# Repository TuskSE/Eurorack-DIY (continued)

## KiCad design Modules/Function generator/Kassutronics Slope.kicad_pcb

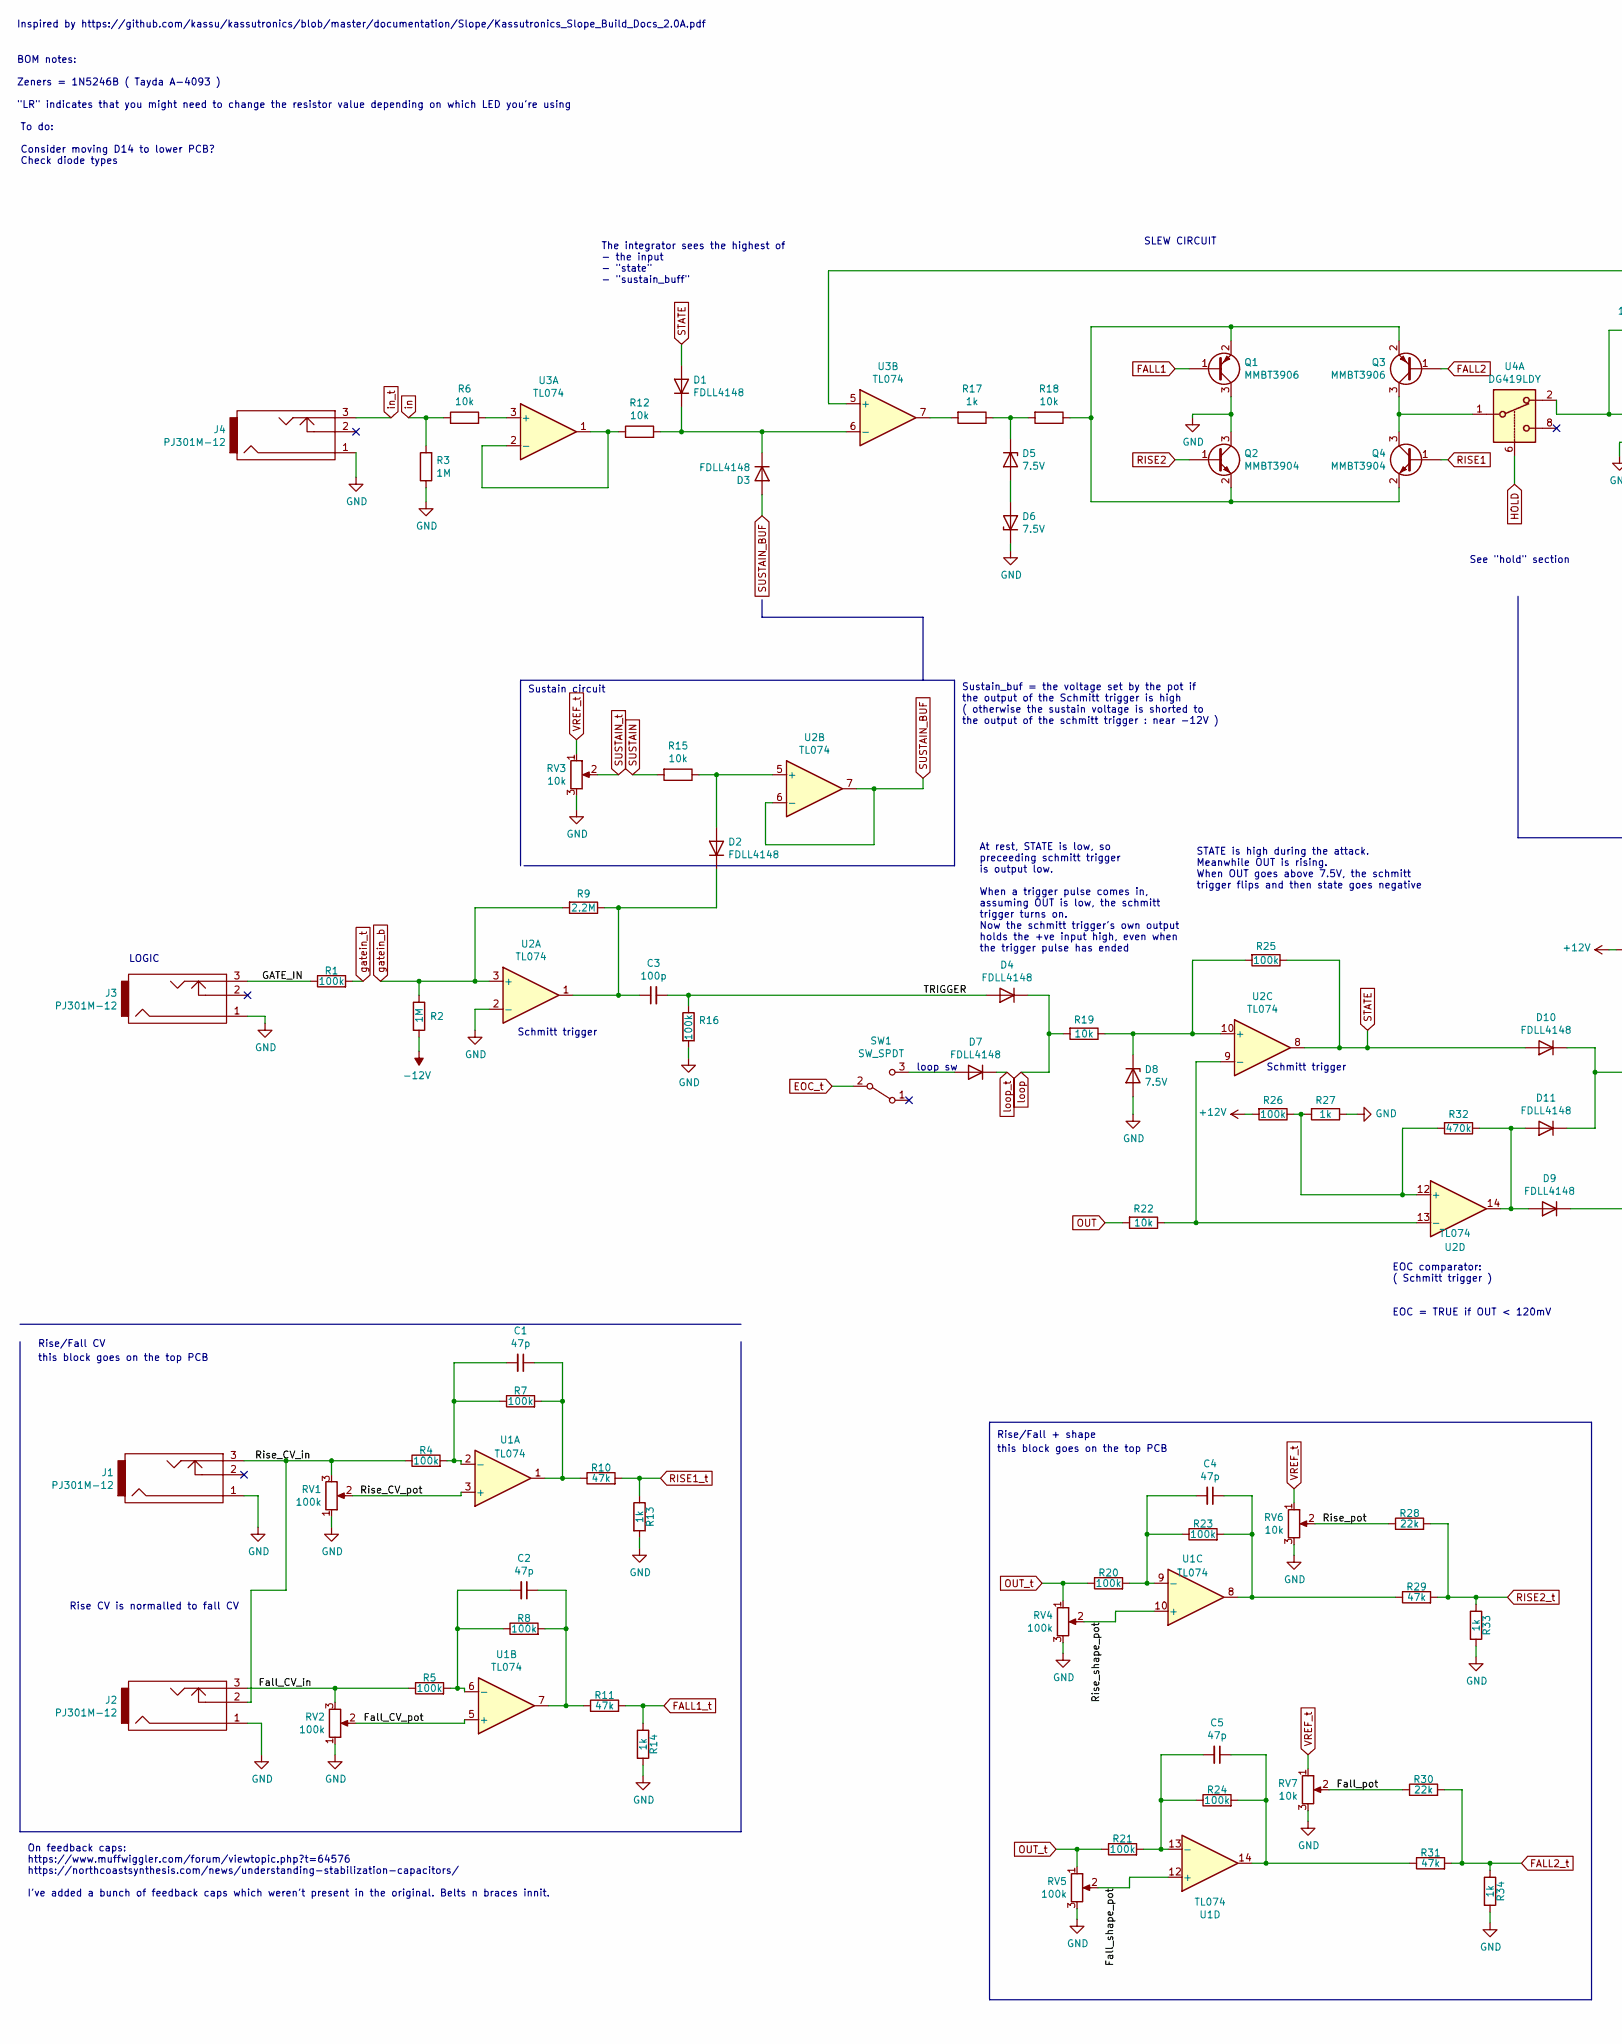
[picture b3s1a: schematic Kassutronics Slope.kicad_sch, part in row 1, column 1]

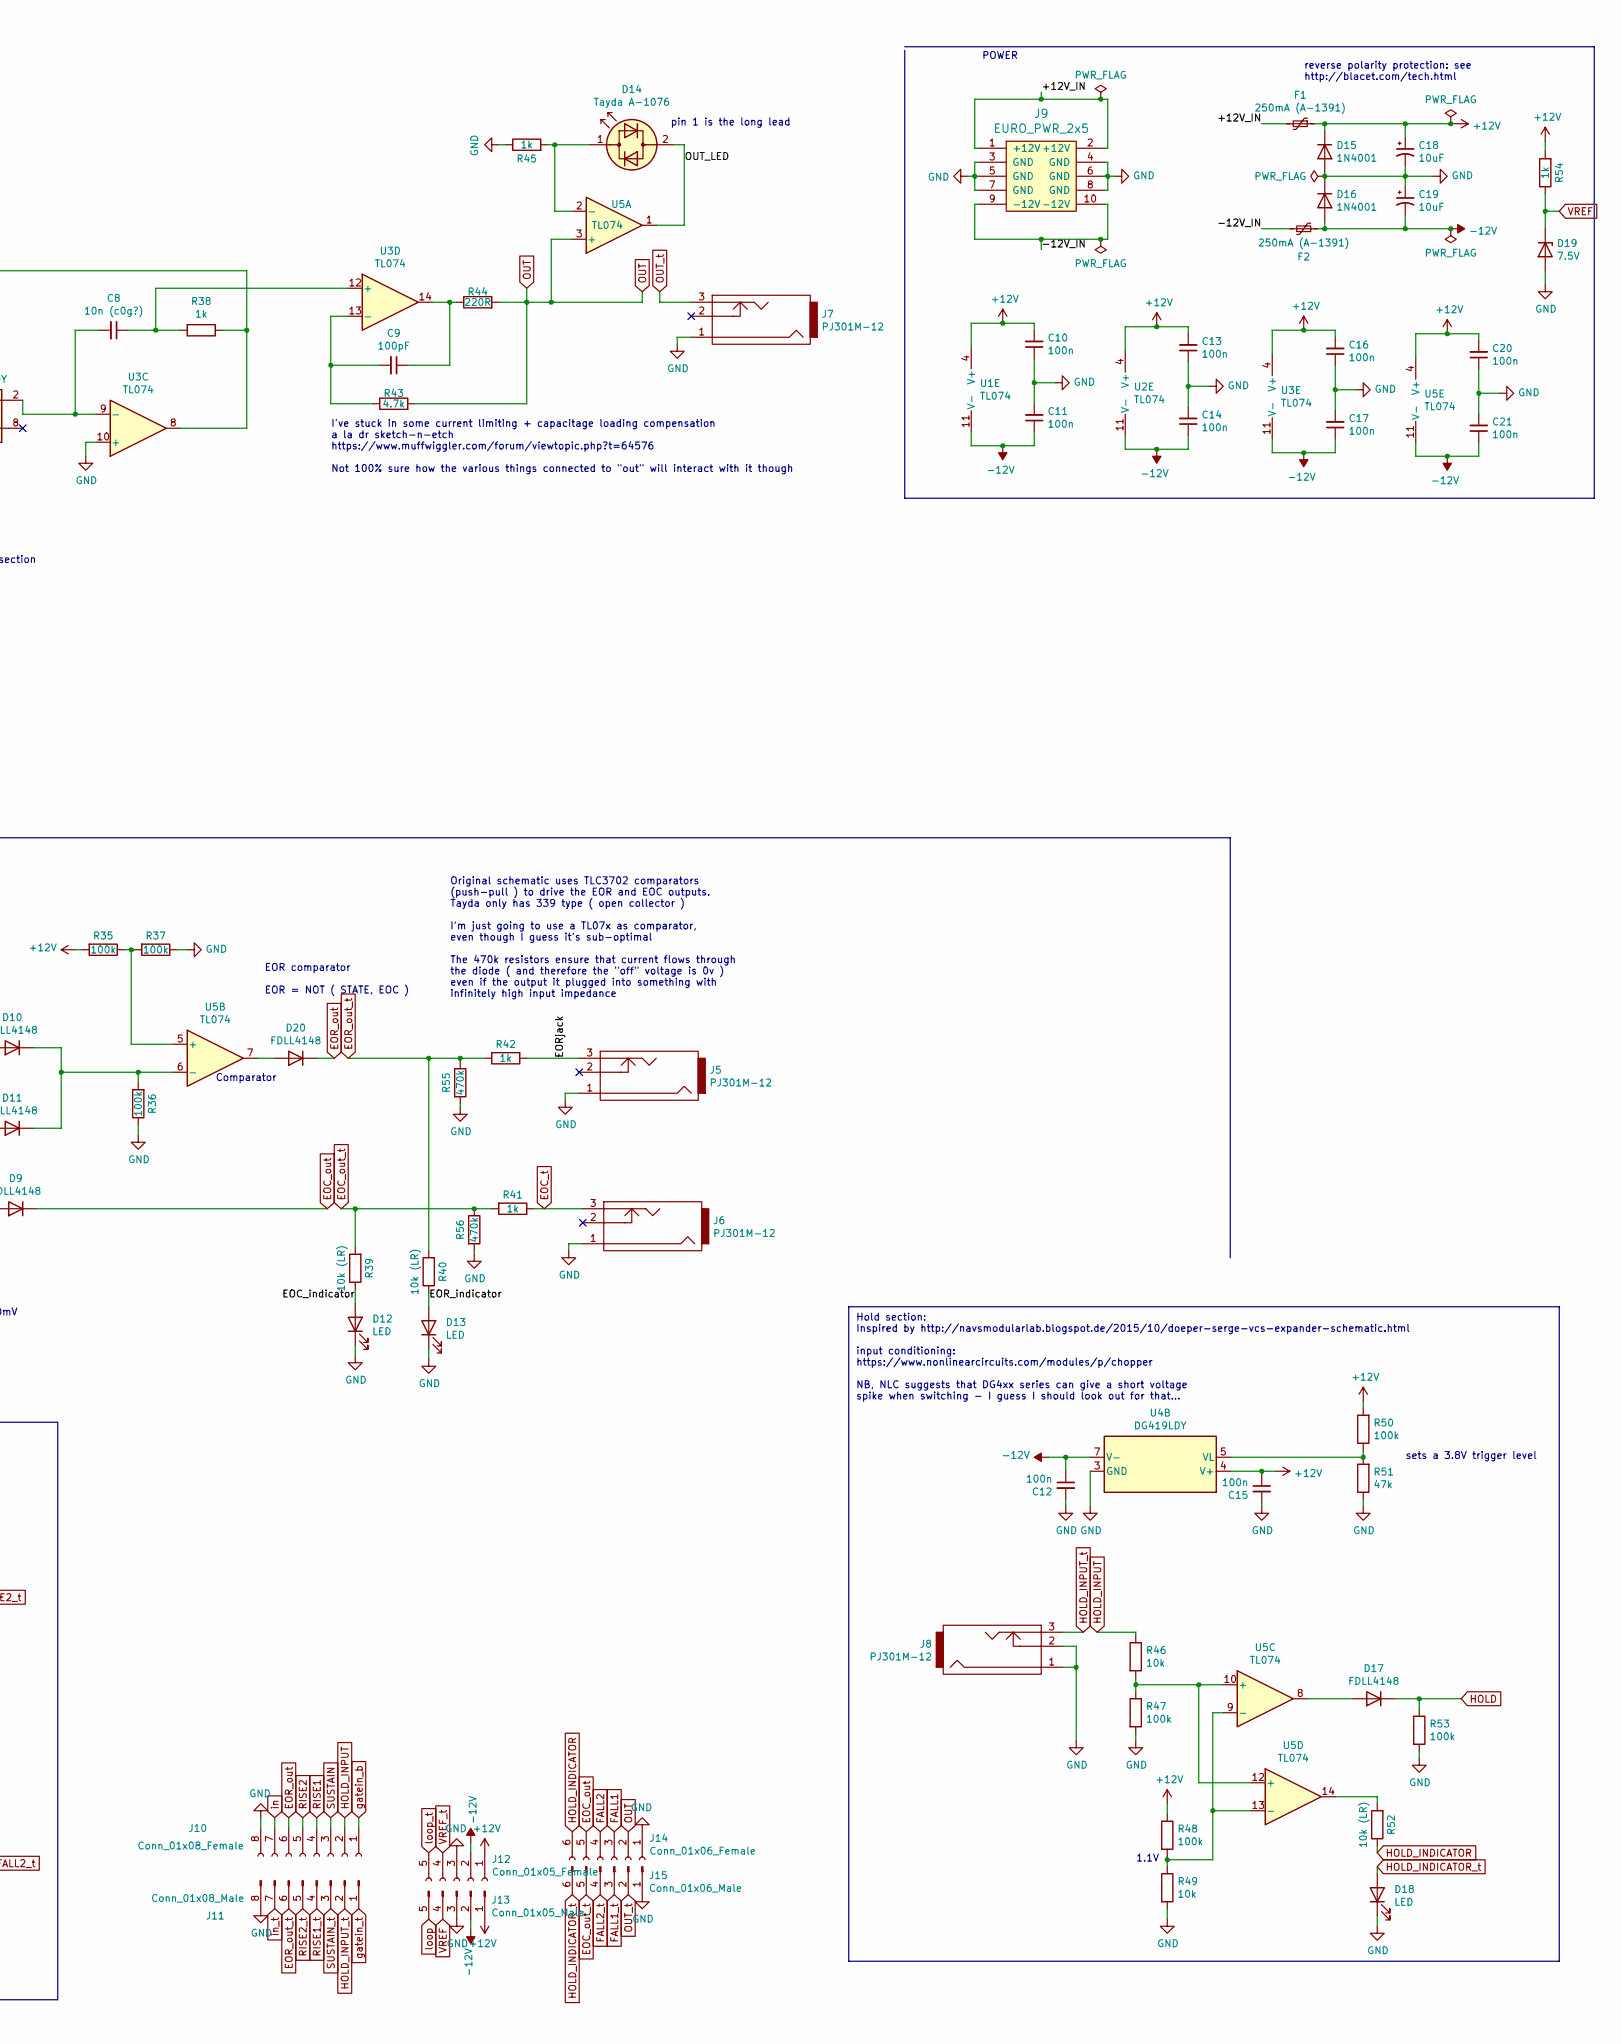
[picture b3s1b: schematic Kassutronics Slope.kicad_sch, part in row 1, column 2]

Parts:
C1, C2, C4, C5: 47p; C_0805_2012Metric_Pad1.15x1.40mm_HandSolder_smallText
C3: 100p; C_0805_2012Metric_Pad1.15x1.40mm_HandSolder_smallText
C8: 10n (c0g?); C_0805_2012Metric_Pad1.15x1.40mm_HandSolder_smallText
C9: 100pF; C_0805_2012Metric_Pad1.15x1.40mm_HandSolder_smallText
C10, C11, C12, C13, C14, C15, C16, C17, C20, C21: 100n; C_0805_2012Metric_Pad1.15x1.40mm_HandSolder_smallText
C18, C19: 10uF; CP_Radial_D5.0mm_P2.00mm
D1, D2, D3, D4, D7, D9, D10, D11, D17, D20: FDLL4148; LL4148_sam
D5, D6, D8, D19: 7.5V; D_DO-35_SOD27_P7.62mm_Horizontal
D12, D13, D18: LED; LED_D3.0mm
D14: Tayda A-1076; LED_D3.0mm
D15, D16: 1N4001; D_DO-41_SOD81_P10.16mm_Horizontal
F1, F2: 250mA (A-1391); C_Disc_D7.5mm_W2.5mm_P5.00mm
J1, J2, J3, J4, J5, J6, J7, J8: PJ301M-12; PJ301M-12_Compact
J9: EURO_PWR_2x5; Eurorack_power_header
J10: Conn_01x08_Female; PinHeader_1x08_P2.54mm_Vertical
J11: Conn_01x08_Male; PinHeader_1x08_P2.54mm_Vertical
J12: Conn_01x05_Female; PinHeader_1x05_P2.54mm_Vertical
J13: Conn_01x05_Male; PinHeader_1x05_P2.54mm_Vertical
J14: Conn_01x06_Female; PinHeader_1x06_P2.54mm_Vertical
J15: Conn_01x06_Male; PinHeader_1x06_P2.54mm_Vertical
Q1, Q3: MMBT3906; SOT-23
Q2, Q4: MMBT3904; SOT-23
R1, R4, R5, R7, R8, R16, R20, R21, R23, R24, R25, R26, R35, R36, R37, R47, R48, R50, R53: 100k; R_0805_2012Metric_Pad1.15x1.40mm_HandSolder_smallText
R2, R3: 1M; R_0805_2012Metric_Pad1.15x1.40mm_HandSolder_smallText
R6, R12, R15, R18, R19, R22, R46, R49: 10k; R_0805_2012Metric_Pad1.15x1.40mm_HandSolder_smallText
R9: 2.2M; R_0805_2012Metric_Pad1.15x1.40mm_HandSolder_smallText
R10, R11, R29, R31, R51: 47k; R_0805_2012Metric_Pad1.15x1.40mm_HandSolder_smallText
R13, R14, R17, R27, R33, R34, R38, R41, R42, R45, R54: 1k; R_0805_2012Metric_Pad1.15x1.40mm_HandSolder_smallText
R28, R30: 22k; R_0805_2012Metric_Pad1.15x1.40mm_HandSolder_smallText
R32, R55, R56: 470k; R_0805_2012Metric_Pad1.15x1.40mm_HandSolder_smallText
R39, R40, R52: 10k (LR); R_0805_2012Metric_Pad1.15x1.40mm_HandSolder_smallText
R43: 4.7k; R_0805_2012Metric_Pad1.15x1.40mm_HandSolder_smallText
R44: 220R; R_0805_2012Metric_Pad1.15x1.40mm_HandSolder_smallText
RV1, RV2: 100k; Alpha9mmPot
RV3, RV6, RV7: 10k; Alpha9mmPot
RV4, RV5: 100k; SongHuei9mmPot
SW1: SW_SPDT; SPDT toggle on-off-on
U1, U2, U3, U5: TL074; SOIC-14_3.9x8.7mm_P1.27mm
U4: DG419LDY; SOIC-8_3.9x4.9mm_P1.27mm

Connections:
+12V: C10.2, C13.2, C15.1, C16.2, C18.1, C20.2, D15.1 (K), F1.1, J12.1, J13.1, R26.2, R35.2, R48.1, R50.2, R54.2, U1.4 (V+), U2.4 (V+), U3.4 (V+), U4.4 (V+), U5.4 (V+)
-12V: C11.1, C12.1, C14.1, C17.1, C19.2, C21.1, D16.2 (A), F2.2, J12.2, J13.2, R2.2, U1.11 (V-), U2.11 (V-), U3.11 (V-), U4.7 (V-), U5.11 (V-)
/+12V_IN: F1.2, J9.1 (+12V), J9.2 (+12V)
/-12V_IN: F2.1, J9.9 (-12V), J9.10 (-12V)
/EOC_indicator: D12.2 (A), R39.1
/EOR_indicator: D13.2 (A), R40.1
/EORjack: J5.3, R42.1
/Fall_CV_in: J2.3, R5.1, RV2.3
/Fall_CV_pot: RV2.2, U1.5 (+)
/Fall_pot: R30.1, RV7.2
/Fall_shape_pot: RV5.2, U1.12 (+)
/GATE_IN: J3.3, R1.1
/OUT_LED: D14.2 (AK), U5.1
/Rise_CV_in: J1.3, J2.2, R4.1, RV1.3
/Rise_CV_pot: RV1.2, U1.3 (+)
/Rise_pot: R28.1, RV6.2
/Rise_shape_pot: RV4.2, U1.10 (+)
/TRIGGER: C3.2, D4.2 (A), R16.1
EOC_out: D9.1 (K), J14.5
EOC_out_t: J15.5, R39.2, R41.2, R56.1
EOC_t: J6.3, R41.1, SW1.2 (B)
EOR_out: D20.1 (K), J10.6
EOR_out_t: J11.6, R40.2, R42.2, R55.1
FALL1: J14.3, Q1.1 (B)
FALL1_t: J15.3, R11.2, R14.1
FALL2: J14.4, Q3.1 (B)
FALL2_t: J15.4, R30.2, R31.2, R34.1
GND: C10.1, C11.2, C12.2, C13.1, C14.2, C15.2, C16.1, C17.2, C18.2, C19.1, C20.1, C21.2, D6.1 (K), D8.2 (A), D12.1 (K), D13.1 (K), D15.2 (A), D16.1 (K), D18.1 (K), D19.2 (A), J1.1, J2.1, J3.1, J4.1, J5.1, J6.1, J7.1, J8.1, J8.2, J9.3 (GND), J9.4 (GND), J9.5 (GND), J9.6 (GND), J9.7 (GND), J9.8 (GND), J10.8, J11.8, J12.3, J13.3, J14.1, J15.1, Q1.3 (C), Q2.3 (C), R3.1, R13.2, R14.2, R16.2, R27.1, R33.2, R34.2, R36.1, R37.1, R45.1, R47.2, R49.2, R51.1, R53.2, R55.2, R56.2, RV1.1, RV2.1, RV3.3, RV4.3, RV5.3, RV6.3, RV7.3, U2.2 (-), U3.10 (+), U4.3 (GND)
HOLD: D17.1 (K), R53.1, U4.6
HOLD_INDICATOR: J14.6, R52.1
HOLD_INDICATOR_t: D18.2 (A), J15.6
HOLD_INPUT: J10.2, R46.1
HOLD_INPUT_t: J8.3, J11.2
unnamed: C1.1, R7.2, R10.1, U1.1
unnamed: C1.2, R4.2, R7.1, U1.2 (-)
unnamed: C2.1, R8.2, R11.1, U1.7
unnamed: C2.2, R5.2, R8.1, U1.6 (-)
unnamed: C3.1, D2.1 (K), R9.1, U2.1
unnamed: C4.1, R23.2, R29.1, U1.8
unnamed: C4.2, R20.2, R23.1, U1.9 (-)
unnamed: C5.1, R24.2, R31.1, U1.14
unnamed: C5.2, R21.2, R24.1, U1.13 (-)
unnamed: C8.1, R38.2, U3.12 (+)
unnamed: C8.2, U3.9 (-), U4.2
unnamed: C9.1, R44.1, U3.14
unnamed: C9.2, R43.1, U3.13 (-)
unnamed: D1.1 (K), D3.1 (K), R12.2, U3.6 (-)
unnamed: D2.2 (A), R15.1, U2.5 (+)
unnamed: D5.1 (K), R17.1, R18.2
unnamed: D5.2 (A), D6.2 (A)
unnamed: D7.2 (A), SW1.3 (C)
unnamed: D8.1 (K), R19.1, R25.2, U2.10 (+)
unnamed: D10.1 (K), D11.1 (K), R36.2, U5.6 (-)
unnamed: D9.2 (A), D11.2 (A), R32.1, U2.14
unnamed: D14.1 (KA), R45.2, U5.2 (-)
unnamed: D17.2 (A), U5.8
unnamed: D20.2 (A), U5.7
unnamed: Q1.2 (E), Q2.2 (E), Q3.2 (E), Q4.2 (E), R18.1
unnamed: Q3.3 (C), Q4.3 (C), U4.1
unnamed: R6.2, U3.3 (+)
unnamed: R12.1, U3.1, U3.2 (-)
unnamed: R17.2, U3.7
unnamed: R22.1, U2.9 (-), U2.13 (-)
unnamed: R26.1, R27.2, R32.2, U2.12 (+)
unnamed: R35.1, R37.2, U5.5 (+)
unnamed: R38.1, U3.5 (+), U3.8
unnamed: R46.2, R47.1, U5.10 (+), U5.12 (+)
unnamed: R48.2, R49.1, U5.9 (-), U5.13 (-)
unnamed: R50.1, R51.2, U4.5 (VL)
unnamed: R52.2, U5.14
OUT: J14.2, R22.2, R43.2, R44.2, U5.3 (+)
OUT_t: J7.3, J15.2, R20.1, R21.1, RV4.1, RV5.1
RISE1: J10.4, Q4.1 (B)
RISE1_t: J11.4, R10.2, R13.1
RISE2: J10.5, Q2.1 (B)
RISE2_t: J11.5, R28.2, R29.2, R33.1
STATE: D1.2 (A), D10.2 (A), R25.1, U2.8
SUSTAIN: J10.3, R15.2
SUSTAIN_BUF: D3.2 (A), U2.6 (-), U2.7
SUSTAIN_t: J11.3, RV3.2
VREF: D19.1 (K), J13.4, R54.1
VREF_t: J12.4, RV3.1, RV6.1, RV7.1
gatein_b: J10.1, R2.1, R9.2, U2.3 (+)
gatein_t: J11.1, R1.2
in: J10.7, R3.2, R6.1
in_t: J4.3, J11.7
loop: D4.1 (K), J13.5, R19.2
loop_t: D7.1 (K), J12.5

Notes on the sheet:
Hold section: Inspired by http://navsmodularlab.blogspot.de/2015/10/doeper-serge-vcs-expander-schematic.html input conditioning: https://www.nonlinearcircuits.com/modules/p/chopper NB, NLC suggests that DG4xx series can give a short voltage spike when switching - I guess I should look out for that.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
EOC comparator: ( Schmitt trigger ) EOC = TRUE if OUT < 120mV
The integrator sees the highest of - the input - "state" - "sustain_buff"
On feedback caps: https://www.muffwiggler.com/forum/viewtopic.php?t=64576 https://northcoastsynthesis.com/news/understanding-stabilization-capacitors/ I've added a bunch of feedback caps which weren't present in the original. Belts n braces innit.
EOR comparator EOR = NOT ( STATE, EOC )
LOGIC
reverse polarity protection: see http://blacet.com/tech.html
POWER
Rise/Fall + shape
SLEW CIRCUIT
pin 1 is the long lead
this block goes on the top PCB
Sustain_buf = the voltage set by the pot if the output of the Schmitt trigger is high ( otherwise the sustain voltage is shorted to the output of the schmitt trigger : near -12V )
I've stuck in some current limiting + capacitage loading compensation a la dr sketch-n-etch https://www.muffwiggler.com/forum/viewtopic.php?t=64576 Not 100% sure how the various things connected to "out" will interact with it though
Inspired by https://github.com/kassu/kassutronics/blob/master/documentation/Slope/Kassutronics_Slope_Build_Docs_2.0A.pdf
Schmitt trigger
Rise/Fall CV
1.1V
Sustain circuit
Rise CV is normalled to fall CV
loop sw
sets a 3.8V trigger level
BOM notes: Zeners = 1N5246B ( Tayda A-4093 ) "LR" indicates that you might need to change the resistor value depending on which LED you're using
See "hold" section
STATE is high during the attack. Meanwhile OUT is rising. When OUT goes above 7.5V, the schmitt trigger flips and then state goes negative
Comparator
At rest, STATE is low, so preceeding schmitt trigger is output low. When a trigger pulse comes in, assuming OUT is low, the schmitt trigger turns on. Now the schmitt trigger's own output holds the +ve input high, even when the trigger pulse has ended
Original schematic uses TLC3702 comparators (push-pull ) to drive the EOR and EOC outputs. Tayda only has 339 type ( open collector ) I'm just going to use a TL07x as comparator, even though I guess it's sub-optimal The 470k resistors ensure that current flows through the diode ( and therefore the 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
To do: Consider moving D14 to lower PCB? Check diode types

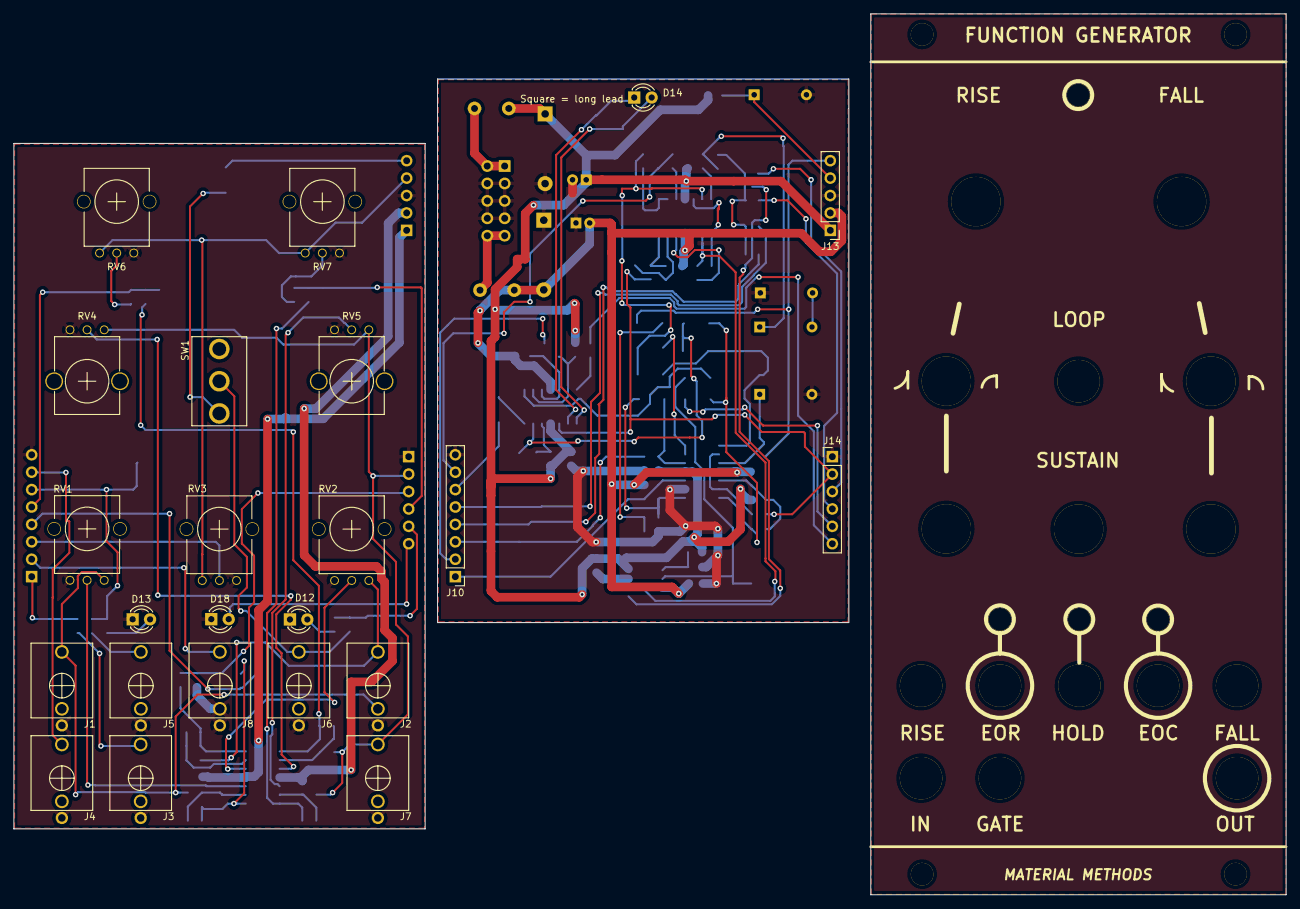
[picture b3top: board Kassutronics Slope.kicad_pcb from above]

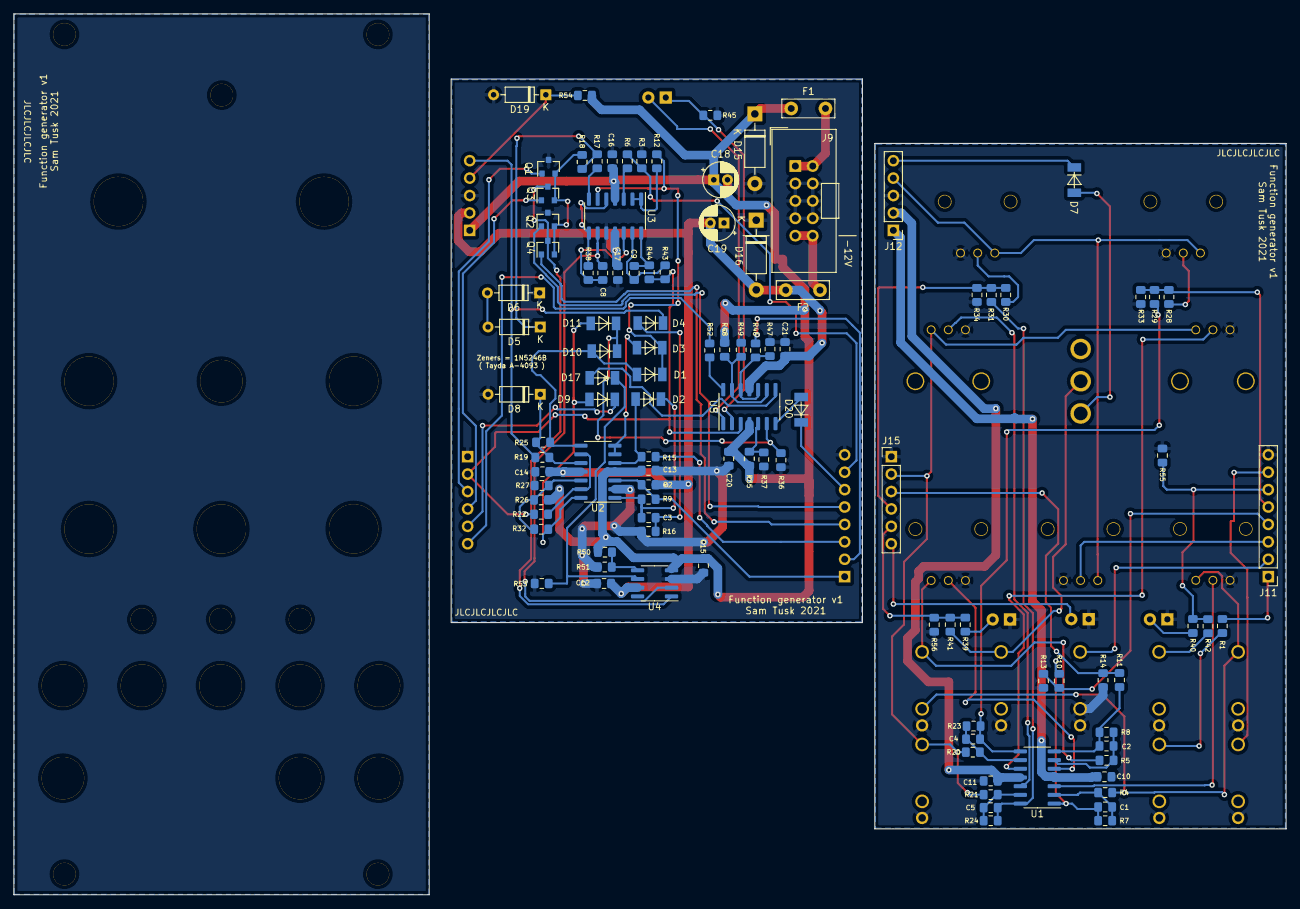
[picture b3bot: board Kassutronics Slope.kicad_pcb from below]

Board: 2 copper layers, 185.6 x 128.5 mm, 129 parts (106 on the bottom side), 88 nets.

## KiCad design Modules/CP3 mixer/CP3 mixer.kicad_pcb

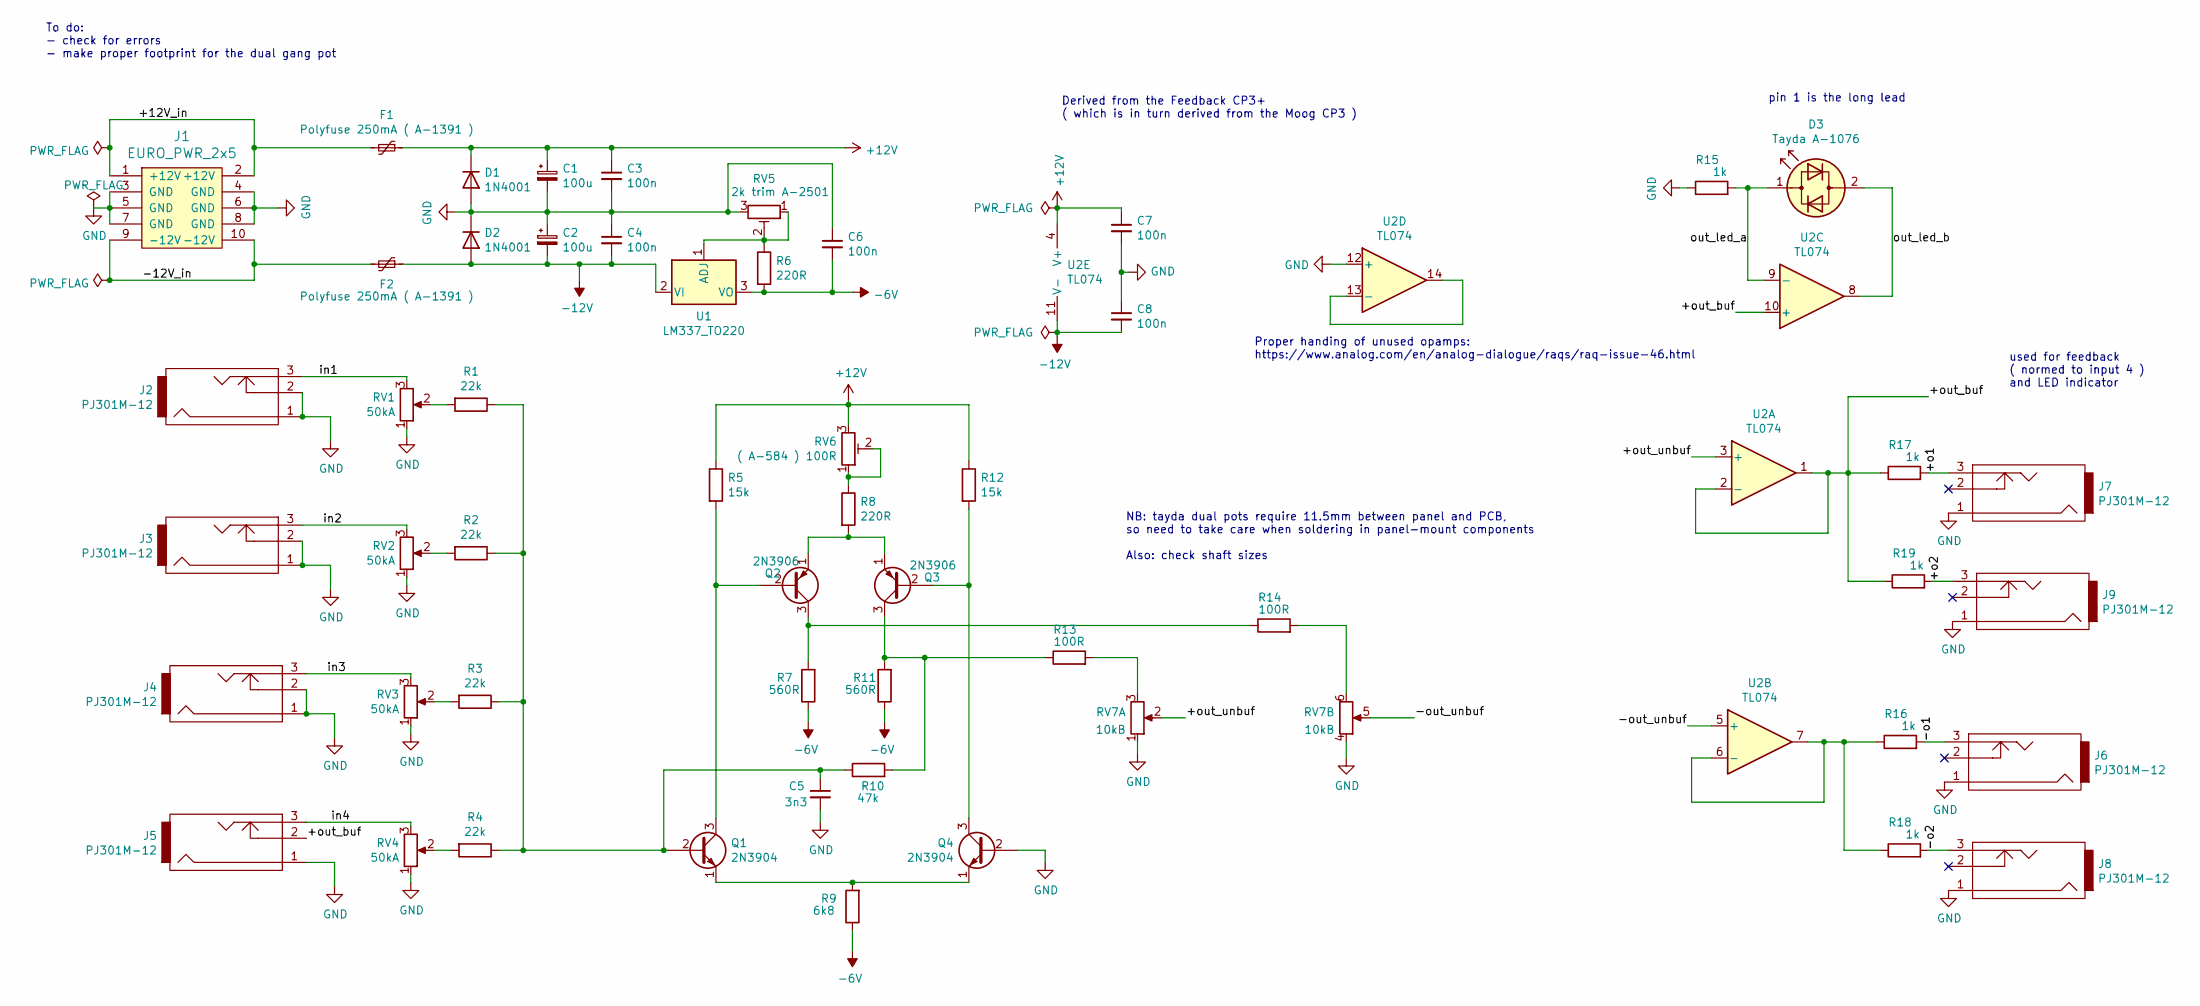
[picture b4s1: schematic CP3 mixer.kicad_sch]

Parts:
C1, C2: 100u; CP_Radial_D6.3mm_P2.50mm
C3, C4, C6, C7, C8: 100n; C_0805_2012Metric_Pad1.15x1.40mm_HandSolder_SmallTxt
C5: 3n3; C_0805_2012Metric_Pad1.15x1.40mm_HandSolder_SmallTxt
D1, D2: 1N4001; D_DO-41_SOD81_P10.16mm_Horizontal
D3: Tayda A-1076; LED_D3.0mm
F1, F2: Polyfuse 250mA ( A-1391 ); C_Disc_D7.5mm_W2.5mm_P5.00mm
J1: EURO_PWR_2x5; Eurorack_power_header
J2, J3, J4, J5, J6, J7, J8, J9: PJ301M-12; PJ301M-12_Compact
Q1, Q4: 2N3904; TO-92_HandSolder
Q2, Q3: 2N3906; TO-92_HandSolder
R1, R2, R3, R4: 22k; R_0805_2012Metric_Pad1.15x1.40mm_HandSolder_smallText
R5, R12: 15k; R_0805_2012Metric_Pad1.15x1.40mm_HandSolder_smallText
R6, R8: 220R; R_0805_2012Metric_Pad1.15x1.40mm_HandSolder_smallText
R7, R11: 560R; R_0805_2012Metric_Pad1.15x1.40mm_HandSolder_smallText
R9: 6k8; R_0805_2012Metric_Pad1.15x1.40mm_HandSolder_smallText
R10: 47k; R_0805_2012Metric_Pad1.15x1.40mm_HandSolder_smallText
R13, R14: 100R; R_0805_2012Metric_Pad1.15x1.40mm_HandSolder_smallText
R15, R16, R17, R18, R19: 1k; R_0805_2012Metric_Pad1.15x1.40mm_HandSolder_smallText
RV1, RV2, RV3, RV4: 50kA; Alpha9mmPot
RV5: 2k trim A-2501; Potentiometer_Runtron_RM-065_Vertical
RV6: ( A-584 ) 100R; Potentiometer_Bourns_3296W_Vertical
RV7: 10kB; RV dual pot
U1: LM337_TO220; TO-220-3_Vertical
U2: TL074; SOIC-14_3.9x8.7mm_P1.27mm

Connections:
+12V: C1.1, C3.1, C7.1, D1.1 (K), F1.1, R5.1, R12.1, RV6.3, U2.4 (V+)
-6V: C6.2, R6.2, R7.1, R9.1, R11.1, U1.3 (VO)
-12V: C2.2, C4.2, C8.2, D2.2 (A), F2.1, U1.2 (VI), U2.11 (V-)
/+12V_in: F1.2, J1.1 (+12V), J1.2 (+12V)
/+o1: J7.3, R17.2
/+o2: J9.3, R19.2
/+out_buf: J5.2, R17.1, R19.1, U2.1, U2.2 (-), U2.10 (+)
/+out_unbuf: RV7.2, U2.3 (+)
/-12V_in: F2.2, J1.9 (-12V), J1.10 (-12V)
/-o1: J6.3, R16.2
/-o2: J8.3, R18.2
/-out_unbuf: RV7.5, U2.5 (+)
/in1: J2.3, RV1.3
/in2: J3.3, RV2.3
/in3: J4.3, RV3.3
/in4: J5.3, RV4.3
/out_led_a: D3.1 (KA), R15.2, U2.9 (-)
/out_led_b: D3.2 (AK), U2.8
GND: C1.2, C2.1, C3.2, C4.1, C5.2, C6.1, C7.2, C8.1, D1.2 (A), D2.1 (K), J1.3 (GND), J1.4 (GND), J1.5 (GND), J1.6 (GND), J1.7 (GND), J1.8 (GND), J2.1, J2.2, J3.1, J3.2, J4.1, J4.2, J5.1, J6.1, J7.1, J8.1, J9.1, Q4.2 (B), R15.1, RV1.1, RV2.1, RV3.1, RV4.1, RV5.3, RV7.1, RV7.4, U2.12 (+)
unnamed: C5.1, Q1.2 (B), R1.1, R2.1, R3.1, R4.1, R10.1
unnamed: Q1.1 (E), Q4.1 (E), R9.2
unnamed: Q1.3 (C), Q2.2 (B), R5.2
unnamed: Q2.1 (E), Q3.1 (E), R8.2
unnamed: Q2.3 (C), R7.2, R14.1
unnamed: Q3.2 (B), Q4.3 (C), R12.2
unnamed: Q3.3 (C), R10.2, R11.2, R13.1
unnamed: R1.2, RV1.2
unnamed: R2.2, RV2.2
unnamed: R3.2, RV3.2
unnamed: R4.2, RV4.2
unnamed: R6.1, RV5.1, RV5.2, U1.1 (ADJ)
unnamed: R8.1, RV6.1, RV6.2
unnamed: R13.2, RV7.3
unnamed: R14.2, RV7.6
unnamed: R16.1, R18.1, U2.6 (-), U2.7
unnamed: U2.13 (-), U2.14

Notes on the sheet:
Proper handing of unused opamps: https://www.analog.com/en/analog-dialogue/raqs/raq-issue-46.html
pin 1 is the long lead
used for feedback ( normed to input 4 ) and LED indicator
NB: tayda dual pots require 11.5mm between panel and PCB, so need to take care when soldering in panel-mount components Also: check shaft sizes
To do: - check for errors - make proper footprint for the dual gang pot
Derived from the Feedback CP3+ ( which is in turn derived from the Moog CP3 )

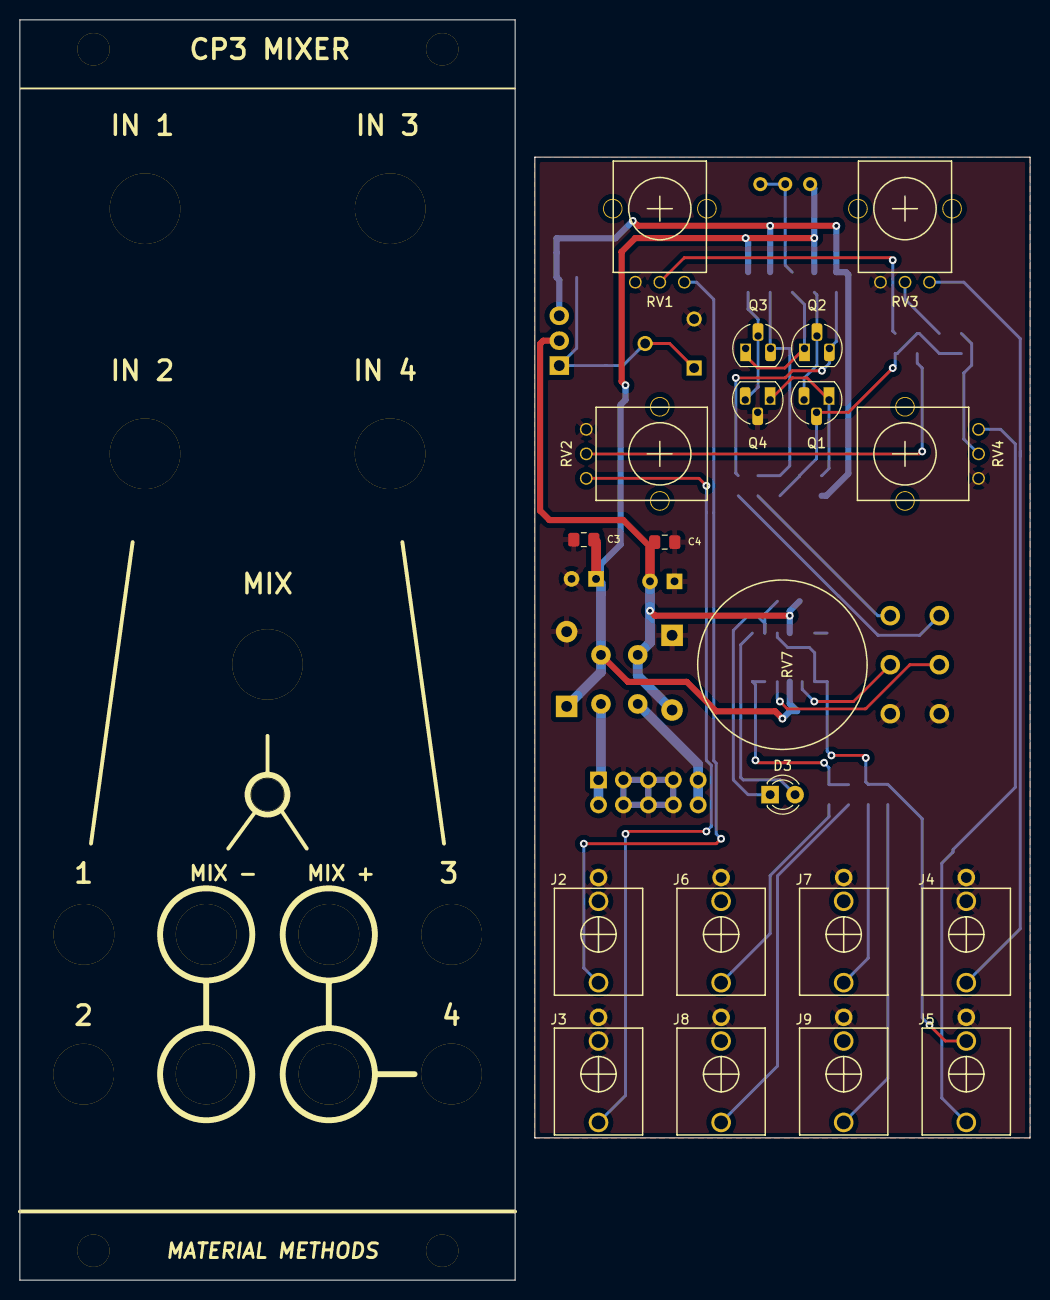
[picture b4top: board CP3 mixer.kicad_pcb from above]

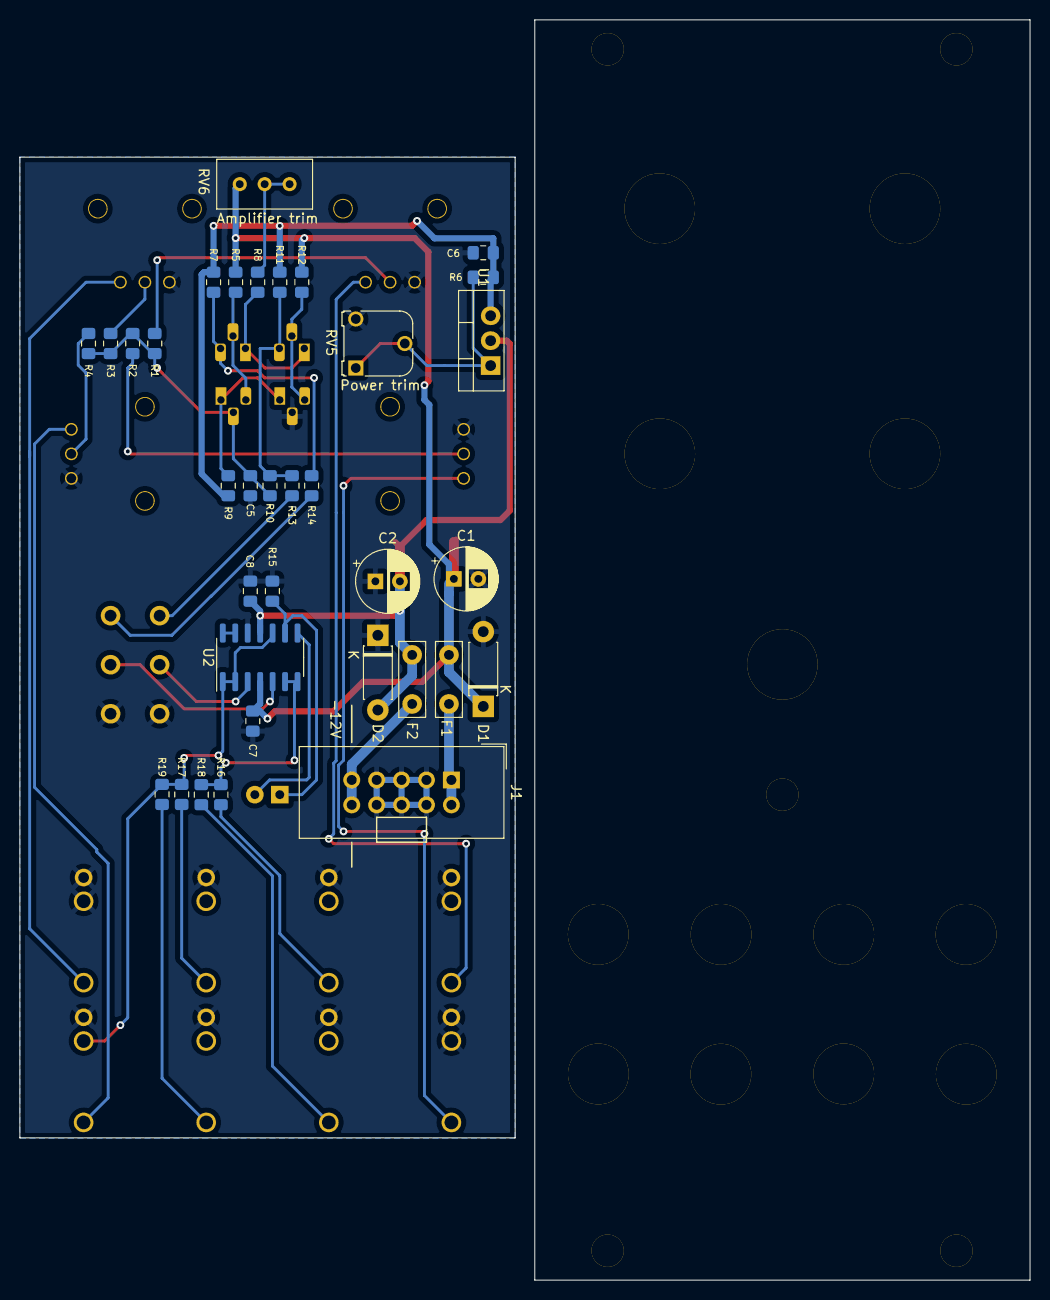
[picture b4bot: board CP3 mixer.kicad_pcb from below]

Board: 2 copper layers, 103.0 x 128.5 mm, 67 parts (34 on the bottom side), 36 nets.

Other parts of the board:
Ref**: Eurorack jack hole; Eurorack_jack_hole
Ref**#2, Ref**#3, Ref**#4, Ref**#5, Ref**#6, Ref**#7, Ref**#8: Eurorack jack hole; Eurorack_jack_hole
Ref**#9: Pothole_Davies1900H_red
Ref**#10, Ref**#11, Ref**#12, Ref**#13: Pothole_Davies1900H_white
